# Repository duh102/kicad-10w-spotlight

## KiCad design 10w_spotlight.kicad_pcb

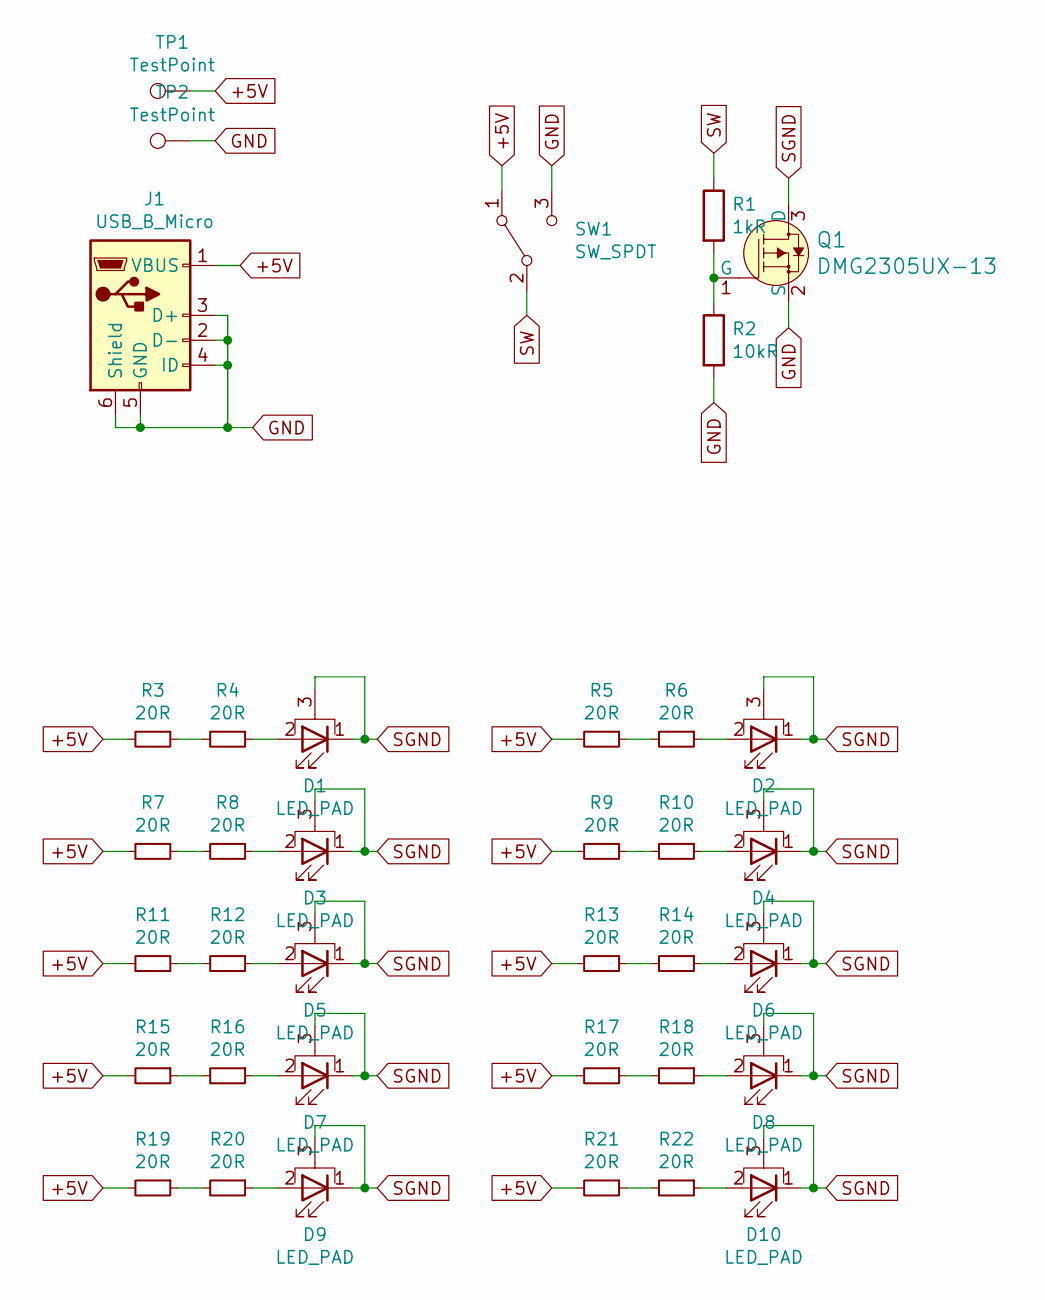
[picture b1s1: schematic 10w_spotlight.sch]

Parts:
D1, D2, D3, D4, D5, D6, D7, D8, D9, D10: LED_PAD; LED_1W_3W_R8
J1: USB_B_Micro; USB_Micro_B_Female_10118194-0001LF
Q1: DMG2305UX-13; SOT-23-3; MPN DMG2305UX-13; Digi-Key_PN DMG2305UX-13DICT-ND
R1: 1kR; R_0805_2012Metric
R2: 10kR; R_0805_2012Metric
R3, R4, R5, R6, R7, R8, R9, R10, R11, R12, R13, R14, R15, R16, R17, R18, R19, R20, R21, R22: 20R; R_0805_2012Metric
SW1: SW_SPDT; SW_Slide_1P2T_CK_OS102011MS2Q
TP1, TP2: TestPoint; TestPoint_Pad_2.0x2.0mm

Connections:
+5V: J1.1 (VBUS), R3.2, R5.2, R7.2, R9.2, R11.2, R13.2, R15.2, R17.2, R19.2, R21.2, SW1.1 (A), TP1.1; also elsewhere on the board
GND: J1.2 (D-), J1.3 (D+), J1.4 (ID), J1.5 (GND), J1.6 (Shield), Q1.2 (S), R2.2, SW1.3 (C), TP2.1; also elsewhere on the board
unnamed: D1.2 (A), R4.1
unnamed: D2.2 (A), R6.1
unnamed: D3.2 (A), R8.1
unnamed: D4.2 (A), R10.1
unnamed: D5.2 (A), R12.1
unnamed: D6.2 (A), R14.1
unnamed: D7.2 (A), R16.1
unnamed: D8.2 (A), R18.1
unnamed: D9.2 (A), R20.1
unnamed: D10.2 (A), R22.1
unnamed: Q1.1 (G), R1.2, R2.1
unnamed: R3.1, R4.2
unnamed: R5.1, R6.2
unnamed: R7.1, R8.2
unnamed: R9.1, R10.2
unnamed: R11.1, R12.2
unnamed: R13.1, R14.2
unnamed: R15.1, R16.2
unnamed: R17.1, R18.2
unnamed: R19.1, R20.2
unnamed: R21.1, R22.2
SGND: D1.1 (K), D1.3 (PAD), D2.1 (K), D2.3 (PAD), D3.1 (K), D3.3 (PAD), D4.1 (K), D4.3 (PAD), D5.1 (K), D5.3 (PAD), D6.1 (K), D6.3 (PAD), D7.1 (K), D7.3 (PAD), D8.1 (K), D8.3 (PAD), D9.1 (K), D9.3 (PAD), D10.1 (K), D10.3 (PAD), Q1.3 (D)
SW: R1.1, SW1.2 (B)

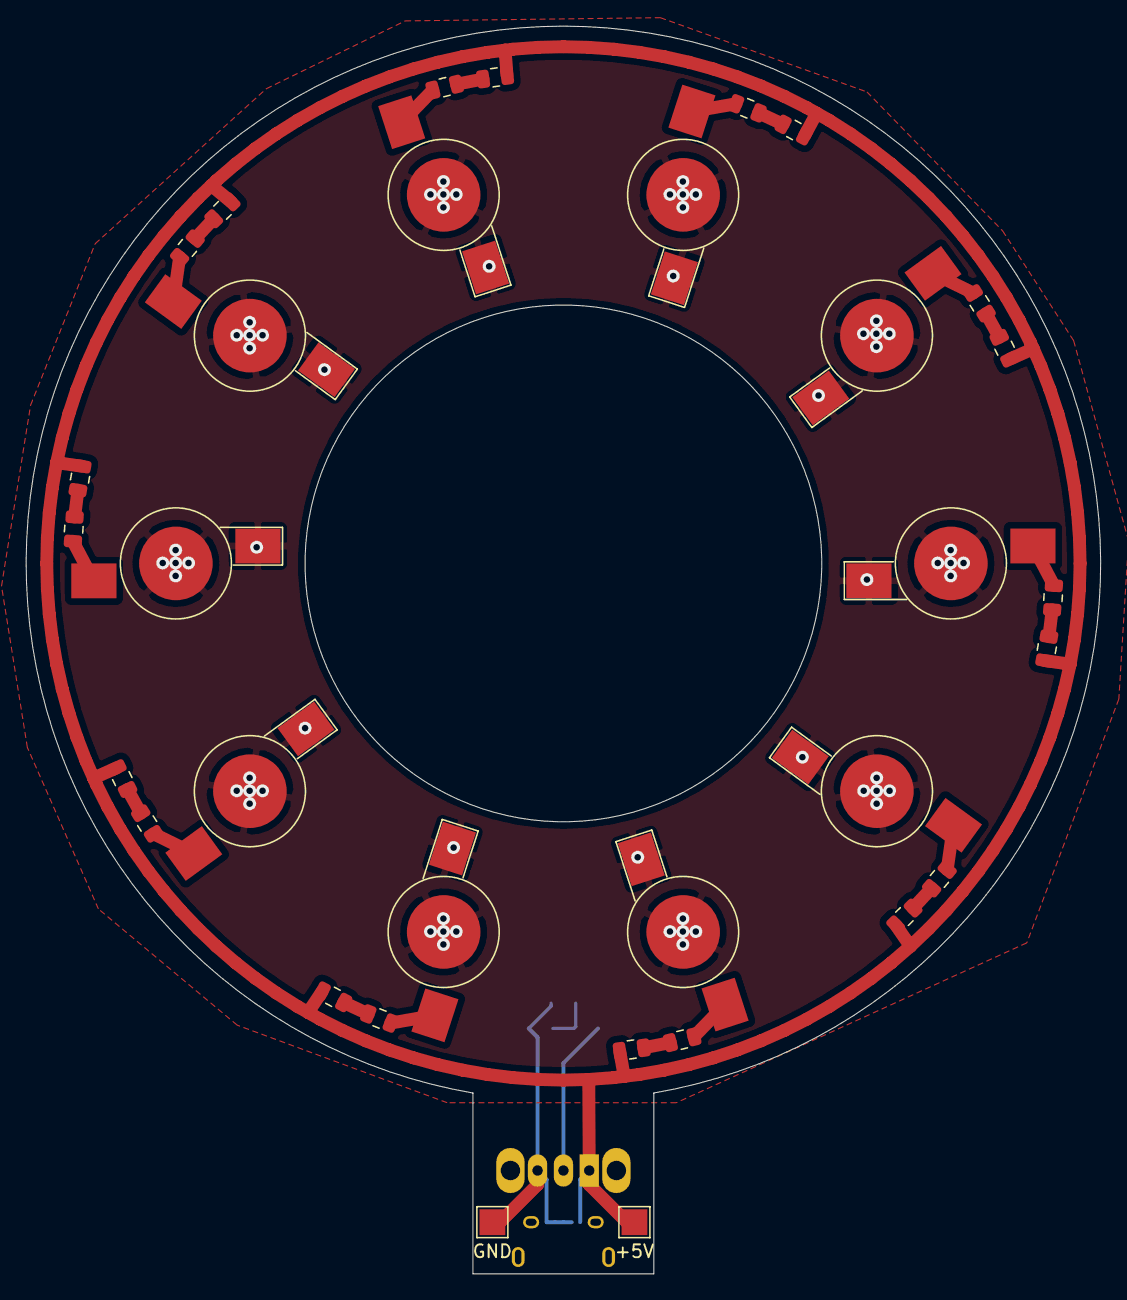
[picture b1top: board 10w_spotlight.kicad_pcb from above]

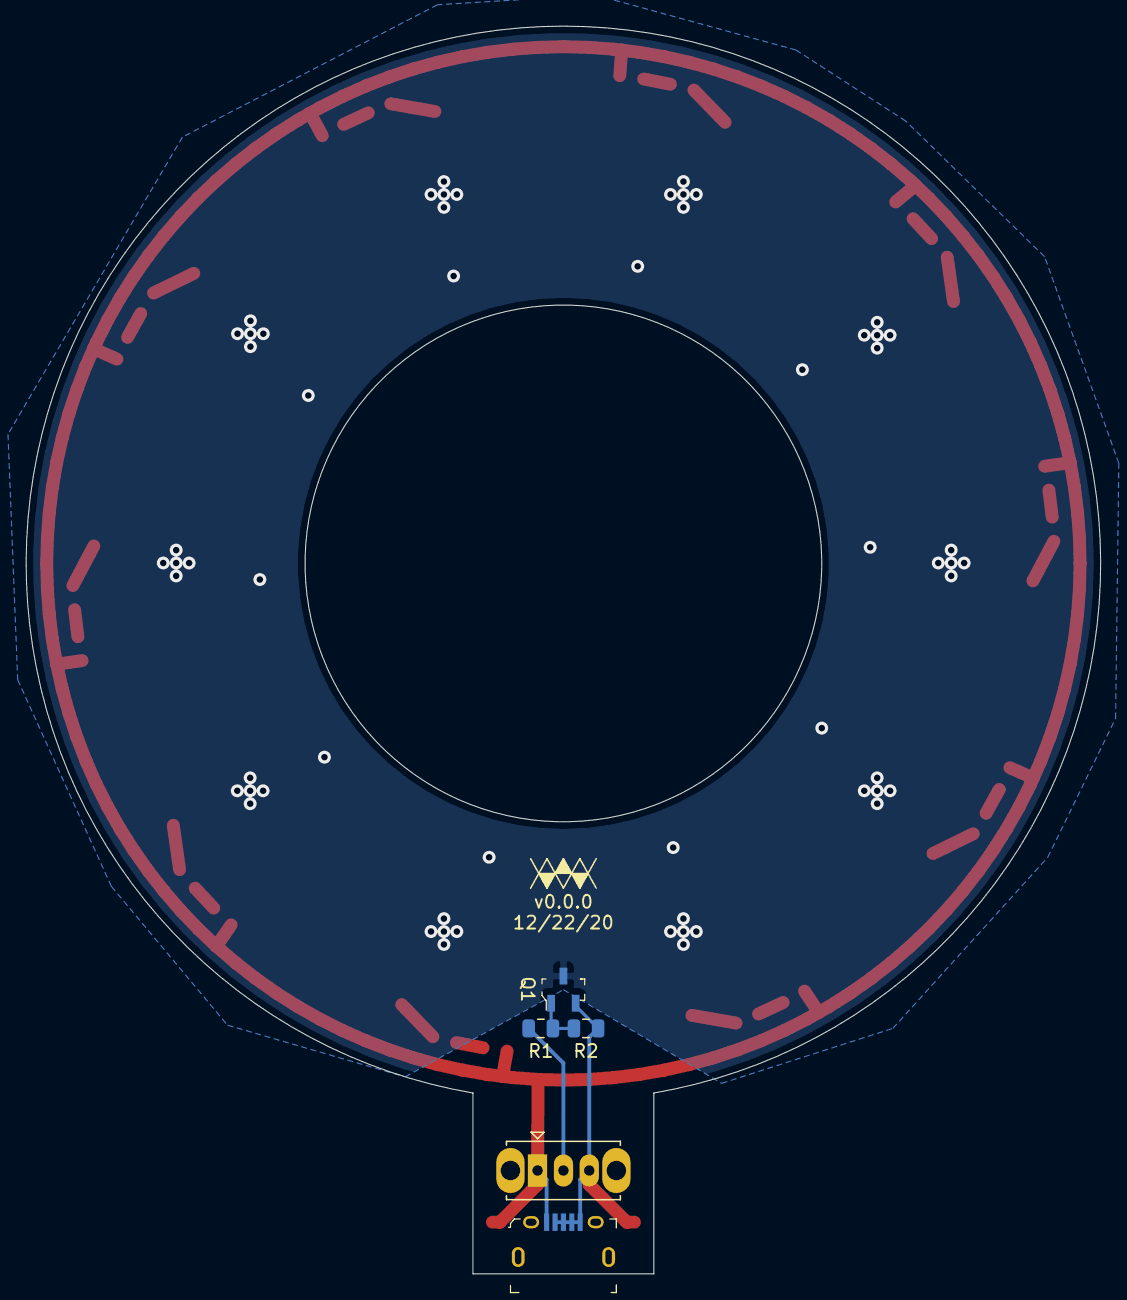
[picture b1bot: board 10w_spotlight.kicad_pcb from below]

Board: 2 copper layers, 83.2 x 96.6 mm, 37 parts (5 on the bottom side), 25 nets.

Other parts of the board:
+5V: TestPoint; TestPoint_Pad_2.0x2.0mm
GND: TestPoint; TestPoint_Pad_2.0x2.0mm

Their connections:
+5V: +5V.1; also elsewhere on the board
GND: GND.1; also elsewhere on the board
